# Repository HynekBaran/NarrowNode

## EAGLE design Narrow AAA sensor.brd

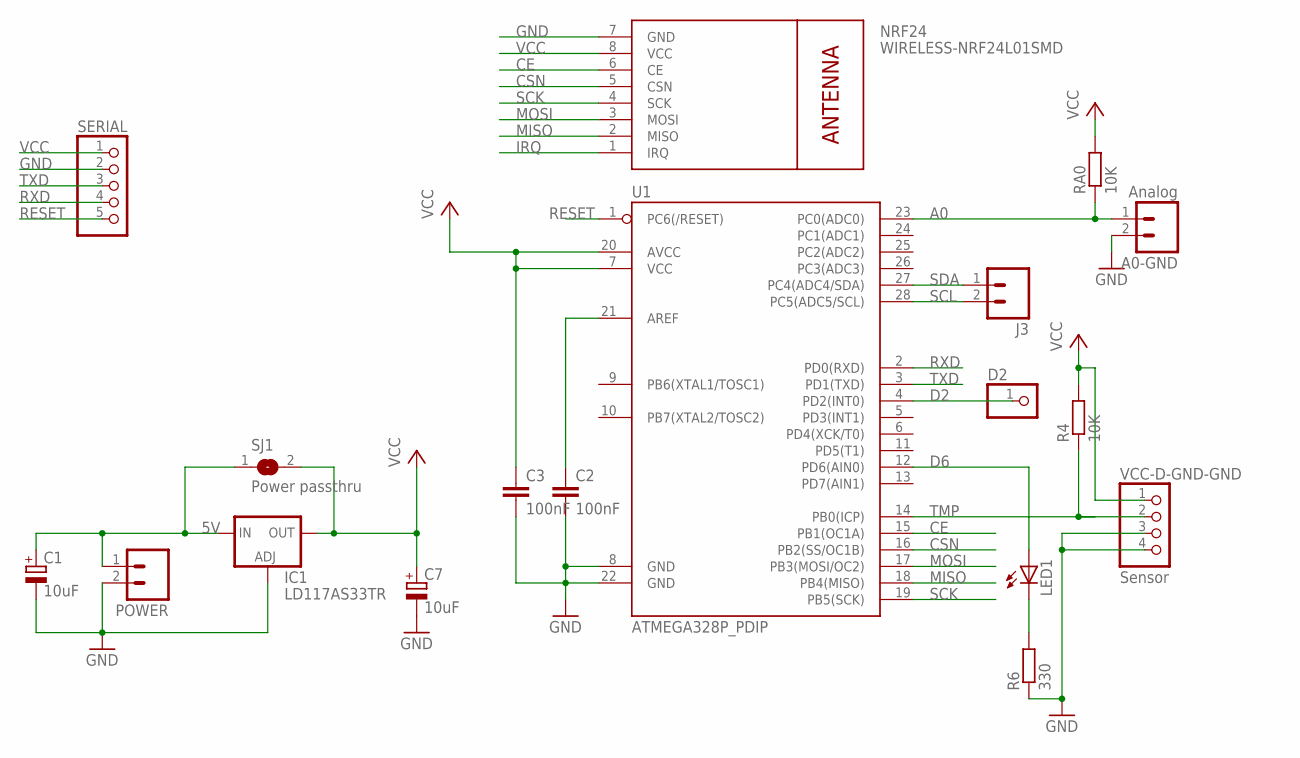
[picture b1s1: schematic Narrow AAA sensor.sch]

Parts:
A0-GND: Analog; 1X02
C1, C7: 10uF; E2,5-5
C2, C3: 100nF; C025-025X050
D2: PINHD-1X1; 1X01
IC1: LD117AS33TR; SOT223
J3: M021X02_NO_SILK; 1X02_NO_SILK
LED1: LED3MM
NRF24: WIRELESS-NRF24L01SMD; WIRELESS-NRF24L01-SMD
POWER: M021X02_NO_SILK; 1X02_NO_SILK
R4: 10K; 0204/7
R6: 330; 0204/7
RA0: 10K; 0204/7
SERIAL: PINHD-1X5; 1X05
SJ1: Power passthru; SJ
U1: ATMEGA328P_PDIP; DIL28-3
VCC-D-GND-GND: Sensor; 1X04

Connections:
5V: C1.+, IC1.3 (IN), POWER.1, SJ1.1
A0: A0-GND.1, RA0.1, U1.23 (PC0(ADC0))
CE: NRF24.6 (CE), U1.15 (PB1(OC1A))
CSN: NRF24.5 (CSN), U1.16 (PB2(SS/OC1B))
D2: D2.1, U1.4 (PD2(INT0))
D6: LED1.A, U1.12 (PD6(AIN0))
GND: A0-GND.2, C1.-, C2.2, C3.2, C7.-, IC1.1 (ADJ), NRF24.7 (GND), POWER.2, R6.1, SERIAL.2, U1.8 (GND), U1.22 (GND), VCC-D-GND-GND.3, VCC-D-GND-GND.4
IRQ: NRF24.1 (IRQ)
MISO: NRF24.2 (MISO), U1.18 (PB4(MISO))
MOSI: NRF24.3 (MOSI), U1.17 (PB3(MOSI/OC2))
unnamed: LED1.K (C), R6.2
unnamed: C2.1, U1.21 (AREF)
RESET: SERIAL.5, U1.1 (PC6(/RESET))
RXD: SERIAL.4, U1.2 (PD0(RXD))
SCK: NRF24.4 (SCK), U1.19 (PB5(SCK))
SCL: J3.2, U1.28 (PC5(ADC5/SCL))
SDA: J3.1, U1.27 (PC4(ADC4/SDA))
TMP: R4.1, U1.14 (PB0(ICP)), VCC-D-GND-GND.2
TXD: SERIAL.3, U1.3 (PD1(TXD))
VCC: C3.1, C7.+, IC1.4 (OUT), NRF24.8 (VCC), R4.2, RA0.2, SERIAL.1, SJ1.2, U1.7 (VCC), U1.20 (AVCC), VCC-D-GND-GND.1

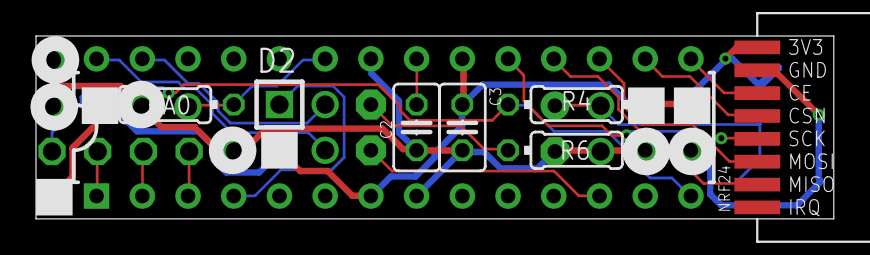
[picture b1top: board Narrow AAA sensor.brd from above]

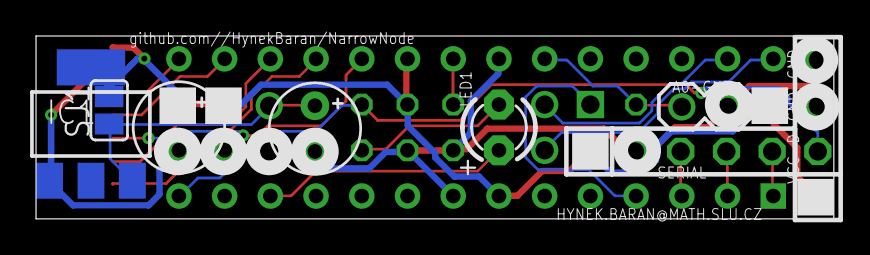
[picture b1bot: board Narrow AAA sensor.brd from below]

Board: 2 copper layers, 44.3 x 10.2 mm, 18 parts (8 on the bottom side), 19 nets.

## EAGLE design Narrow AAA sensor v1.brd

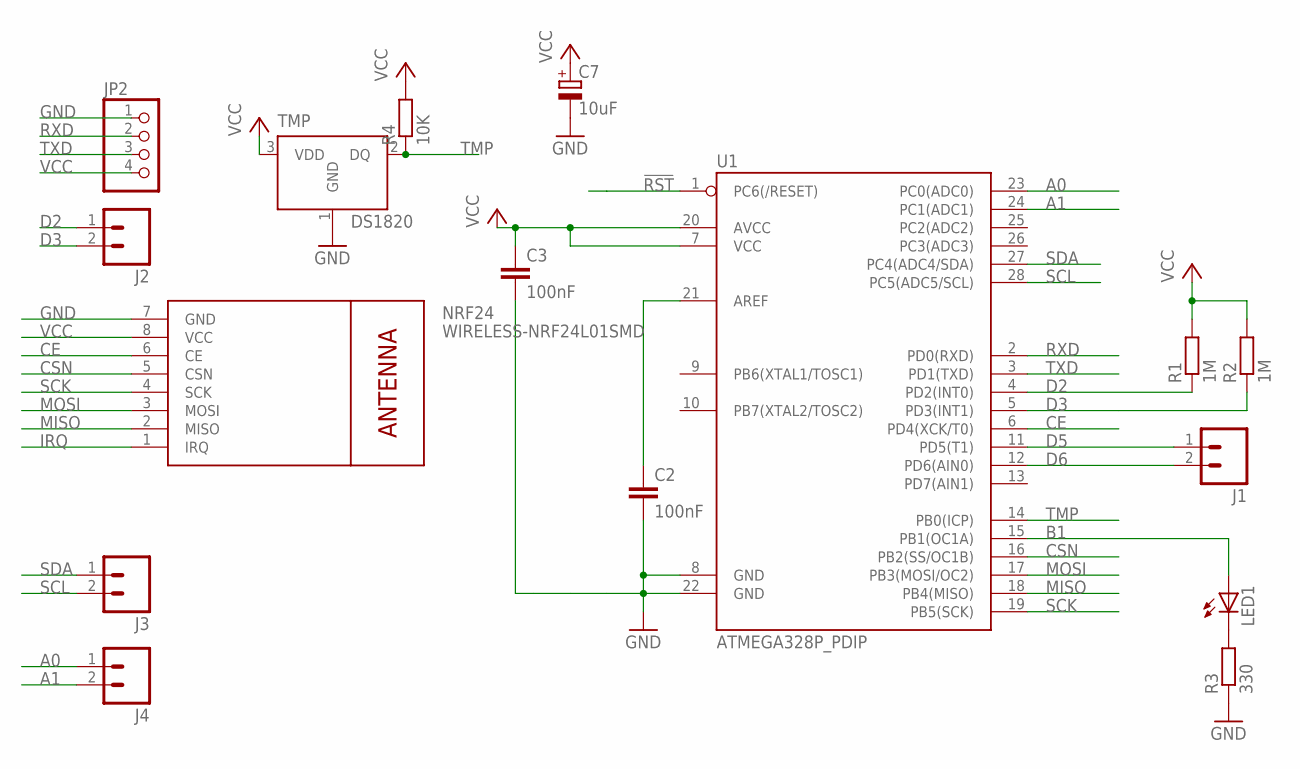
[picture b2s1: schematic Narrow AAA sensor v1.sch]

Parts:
C2, C3: 100nF; C025-025X050
C7: 10uF; E2,5-5
J1, J2: M02PTH; 1X02
J3, J4: M021X02_NO_SILK; 1X02_NO_SILK
JP2: PINHD-1X4; 1X04
LED1: LED3MM
NRF24: WIRELESS-NRF24L01SMD; WIRELESS-NRF24L01-SMD
R1, R2: 1M; 0204/7
R3: 330; 0204/7
R4: 10K; 0204/7
TMP: DS1820; TO-92
U1: ATMEGA328P_PDIP; DIL28-3

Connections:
!RST: U1.1 (PC6(/RESET))
A0: J4.1, U1.23 (PC0(ADC0))
A1: J4.2, U1.24 (PC1(ADC1))
B1: LED1.A, U1.15 (PB1(OC1A))
CE: NRF24.6 (CE), U1.6 (PD4(XCK/T0))
CSN: NRF24.5 (CSN), U1.16 (PB2(SS/OC1B))
D2: J2.1, R1.1, U1.4 (PD2(INT0))
D3: J2.2, R2.1, U1.5 (PD3(INT1))
D5: J1.1, U1.11 (PD5(T1))
D6: J1.2, U1.12 (PD6(AIN0))
GND: C2.2, C3.2, C7.-, JP2.1, NRF24.7 (GND), R3.1, TMP.1 (GND), U1.8 (GND), U1.22 (GND)
IRQ: NRF24.1 (IRQ)
MISO: NRF24.2 (MISO), U1.18 (PB4(MISO))
MOSI: NRF24.3 (MOSI), U1.17 (PB3(MOSI/OC2))
unnamed: LED1.K (C), R3.2
unnamed: C2.1, U1.21 (AREF)
RXD: JP2.2, U1.2 (PD0(RXD))
SCK: NRF24.4 (SCK), U1.19 (PB5(SCK))
SCL: J3.2, U1.28 (PC5(ADC5/SCL))
SDA: J3.1, U1.27 (PC4(ADC4/SDA))
TMP: R4.1, TMP.2 (DQ), U1.14 (PB0(ICP))
TXD: JP2.3, U1.3 (PD1(TXD))
VCC: C3.1, C7.+, JP2.4, NRF24.8 (VCC), R1.2, R2.2, R4.2, TMP.3 (VDD), U1.7 (VCC), U1.20 (AVCC)

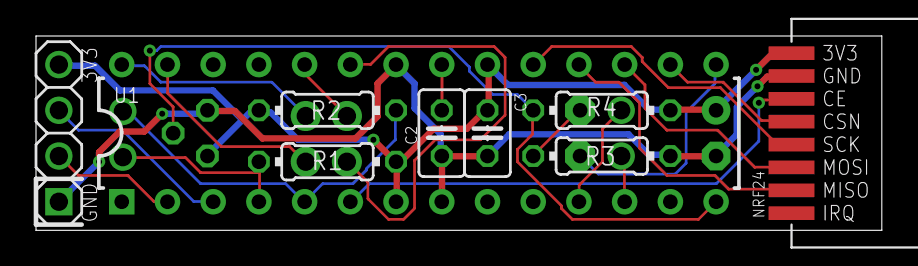
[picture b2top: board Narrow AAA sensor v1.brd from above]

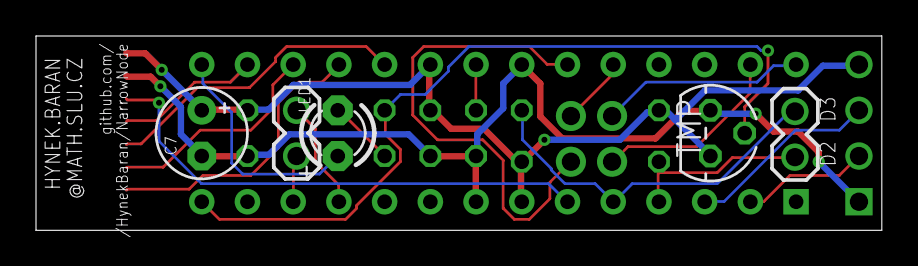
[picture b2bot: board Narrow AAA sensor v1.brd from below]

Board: 2 copper layers, 47.0 x 10.8 mm, 16 parts (5 on the bottom side), 21 nets.

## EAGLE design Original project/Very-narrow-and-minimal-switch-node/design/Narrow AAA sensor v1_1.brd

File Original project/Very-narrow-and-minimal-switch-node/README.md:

**What izz dizz ???**

**_
### Version 1-0:
_**

This board is a 1 trick pony (it's not very smart). It is meant to allow connection of 2 switches on pins D2 and D3 of the processor. It uses the SMD version of the NRF24L01+ module, runs the atmega328p on internal oscillator and is meant to sleep most of the time.

There is space for a pull up resistor (any value between 1M Ohm and 10M Ohm is fine) for each of the two pins (D2 and/or D3).
```
R1 is for D2
R2 is for D3

```
A led is connected to pin D8 via a 330 Ohm resistor (R3). An electrolytical capacitor of 10uF is provided to decouple the Vcc and Gnd pins of the NRF24L01+ smd module. Two 100nF ceramic capacitors are decoupling the power line (Vcc/AVcc and ARef).

And that is it. No temp sensor, no voltage divider, no prototyping area, no FTDI connector, no ISP connector, no crystal.

Just a very narrow node based on @m26872's original idea.

**How can you use it ?**

Since there are two pins for digital signals and 2 pins for power, you still have a few options.

Lets look at the easy part first: power

This boards needs DC power between 1.9V DC (the minimum the NRF24L01+ module needs to function) and maximum 3.6V DC (again a limitation of the NRF24L01+). The processor can handle a wider range (1.8v - 5.1V), but as said, the radio sets the limits on the allowed voltages. There are two pins at the edge called "GND" and "3V3", function should be obvious. GND has a square pad and sits at the edge of the board.

For further orientation, hold the board so that the radio is on the right hand side, the "GND" terminal sits in the top left corner.

Now for the two pins called "D2" and "D3".

These two pins are connected directly to the pins of the processor called ... wait for it ... "D2" and "D3". I'm feeling very pleased with knowing this now :-), moving on.

If you do not mount the pull up resistors, you can use these pins as outputs. Seriously? Yes !!!! Outputs ! We can give "1" or "0" on both D2 and D3 so this could be used for control of something. Personally not my use case, but it is possible.

**1 switch input**

If you need only 1 pin to connect a switch (magnetic, mechanical, reed, optical,...), but you are missing a "GND" pin, then there is a solution.

You do NOT mount the pull up resistor for D3, and define pin D3 as an output LOW pin. This sets D3 equal to ground. You will need to define this in the setup procedure of the sketch.

Then you will need to have mounted the pull up resistor for D2 (on the board it is marked with "R1"), and the header pin called "D2" becomes the input.

You would get the following on the header:

```
square pad: GND    -----+ power terminal, houurrah !
round pad: VCC    ------+
round pad: D2 (input)     -------+
round pad: D3 (= GND)     -------+ switch terminal, yeah !
```

**powering something with low consumption**

You can set both pins D2 and D3 of the processor to OUTPUT, do not mount the pull up resistors, do not activate the internal PullUPs, and by setting one of the pins to HIGH and the other to LOW you can power something. You will need to take care that a maximum of 20mA is consumed, as this is the recommended maximum amperage the pins of the atmega328 can drive or source.

**Now for another option: two switches.**

This is easy to understand: when both pull up resistors are mounted and both the processor pins D2 and D3 are set to INPUT, then the header pins are ready to receive GND or 3V3. You will need to use the power "GND" pin as ground reference.

The nice thing about D2 and D3 as input pins, is that they can be set as hardware interrupt pins to wake up the processor from power down (MySensor "SLEEP(0,CHANGE,1,CHANGE,0)" function).

Power consumption is measured at 7.7 uA maximum during sleep (2 open switches) and 7.0 uA minimum (2 closed switches), if using the Watchdog timer to wake up every now and then to send battery level. Under full power down (as the function call above does) the power consumption will be lower but I did not measure it yet.

This is my preferred use case, hence the name of this node.

**about Passive Infra Red sensing**

If a PIR sensor is powered by 3V3, and it can produce a HIGH signal, you could connect a switch (on a door or window) to pin D2. And you still can connect the PIR to D3. Any change on D2 or D3 would wake up the processor.

Regarding PIR sensors to use: only use 3V3 versions, not the ones which need 5V, because they would drive the input pin too high. Not a disaster if you do this, but I'm not sure how long the atmega328 would accept it before failing.

**Other sensors ???**

Indeed, any other sensor which produces a logical HIGH or LOW can be used as input on D2 or D3. Just make sure that the sensor is powered by itself, or works within the limits of the battery voltage powering the node.

**Measuring and reporting battery voltage**

Battery voltage is measured by using the internal reference and the Vcc library (so no voltage divider needed). My DEV library based sketch is included and uses this library. As we are not allowed to power the board above 3.6V DC, we can use the "hidden" voltage measuring technique. Look at the provided sketch for this (look for "vcc.something").
This internal measuring technique has an error of around 10%, so do not expect accurate readings. Use it to decide when to replace the battery. I set an alarm in my controller, when a node reports a battery level below 2V. This gives me time to go buy batteries and replace them (usually more than a week time between first alarm and replacement, I'm slow ...).

**About the included sketch**

-- important: the sketch was written using the Development library, so not version 1.5.x but the newest of the newest of the best ;-). It may look like some things are missing in the code, that would be true if you have MySensors library 1.5.x

In my sketch, the battery voltage is sent every time the processor wakes up. If nothing changes at the input pins, then the node will wake up every 23 hours to report battery voltage (not battery percent, only battery voltage).
If a signal change is seen at the pins, the battery voltage is measured and sent first. This allows the signal at the input pins to settle to a stable state (this is software debounce), and if the stable state at the pin is different from previous reporting, it is sent to the gateway/controller.

**about the hardware**

You can get this board at OSH Park:

v1-0  https://oshpark.com/shared_projects/LAJtrt2k

v1-1  https://oshpark.com/shared_projects/GTBdUqTV

I'm using a Optiboot 6.2 version which expects a baudrate of 38400. Any boot loader is fine, as long as you set the fuses to 8MHz internal oscillator. You will need to flash the atmega328p before you plug it into this board, so make sure it works in another setup or on the breadboard before you push it hard into the socket.

There is no way to reprogram the board, not via FTDI, not over the air, not by jedi hand waving. Only when you pull out the processor and program it in another setup, can you change anything. Remember: this is a minimal board, it does 1 thing (or 2 if you use two pins), and it can notify your controller of whatever it does or sees. But it is certainly not a versatile node like it's godfather (the slim 2AA battery node by m26872). This is a minion.

**_
### Version 1-1:
_**

In a comment someone suggested to add I2C capability, and actually this is relatively easy. So I added solder jumpers to give the option.

There are two solder jumpers called SJ1 and SJ2. Together they define which signals are presented on PIN1 and PIN2 of the header at the edge of the board.

The silkscreen also shows this. The consequence of this change is that you can not add 2 pull up resistors, but just 1 (for D2). Here are the options.

```
SJ1:
+--SDA-A4
+--PIN1--+
   D2----+
```
With SJ1 you choose to connect either D2 to PIN1 of you choose A4 connected to PIN1. This is independent of the other jumper.
If you want to use I2C, you will need to connect SCL-A5 as well on SJ2.

```
SJ2:
+--SCL-A5
+--PIN2---+
   GND----+
```
With this solder jumper you can connect GND to PIN2, or you choose A5 connected to PIN2. If I2C needs to be used, then A4 needs to be connected, and the I2C functions need to be called.

Here are all possible combinations you can make on the header

```
GND
D2
GND
VCC
```

```
GND
D2
A5
VCC
```

```
GND
A4
GND
VCC
```

```
GND
A4
A5
VCC
```

In this last case you can use the pins as analog inputs, or as the I2C "ports" SDA/SCL:

```
GND
SDA
SCL
VCC
```

This is - by pure coincidence - also the pinout of the small SMD versions of a SI7021 board.

Second remark on I2C: this node does not provide pull up resistors for I2C, so if needed, the connecting device needs to provide the I2C pull up resistors. Most I2C sensor boards do this, but check anyway.

**Using D6**

Version 1-1 of the board is slightly different than v1-0 in another aspect: instead of using pin D8 to allow flashing a LED, I now use pin D6. I have added a bootloader (based on Optiboot 6.2) which will flash the LED on pin D6 three times when reset is given. You can find the hex file in the design files.

Why pin D6 ? Because it can be driven with Pulse Width Modulation via the function AnalogWrite(). Pin D8 is a pure on/off pin.

If you skip mounting R3 and put a wire instead, then you have D6 and GND at the pads where normally one would solder the LED. This means that if you can live without the LED, you actually have access to a third processor pin. In this case D6.

I thought D6 would be more versatile then D8. And for those that do use a LED, D6 allows dimming effects (whereas D8 was only on or off).

**RESET pullup**

Finally, another change between v1-0 and v1-1 is how I handle the reset pin. I left it floating in v1-0. So far that has not caused any problems, except in 1 board. So I decided to pull up RESET just to be sure. As I had to choose between giving GND or a second interrupt cable pin on the external connector, I decided in favour of GND. This node is simple and cheap enough to handle a single switch. Handling 2 switches is possible, but not really needed. And we can still use an analog pin as digital input. And if you skip mounting the LED to get a third pin (input or PWM capable output): D6.

The fact that only 1 pin can wake the node from deep sleep is a tradeoff I accept.

**Version history**

JAN 2016: Added Version 1 info.
This is revision 1 of this board. It is meant as a test board for mounting the SMD version of the NRF24L01+ (a quick hack I admit). A possible improvement is to add two more holes next to R1 and R2, so they could be used as pull down resistors.
The silkscreen (the text on the board) can be better, and marking the names of the header pins on he bottom side is something I should have done (using the boards tells me this now). The numbering of the capacitors does not start at C1, because originally I had more of them on the board. I did not renumber after cleaning out all unnecessary stuff. I may do that at a later stage if I revisit this design.
The designed is licensed under CERN OHL V1.2 and is fully Open Hardware.

13-FEB-2016: added v1-1 files (tested) and use cases.
Explanation of the solder jumpers and what you could do with the pins in various combinations.
15-FEB-2016: added bootloader
Added a recompiled Optiboot 6.2 with LED flash on pin D6, for 8MHz internal oscillator (or 8MHz crystal if you use this in another board) and baudrate of 38400 for uploads.

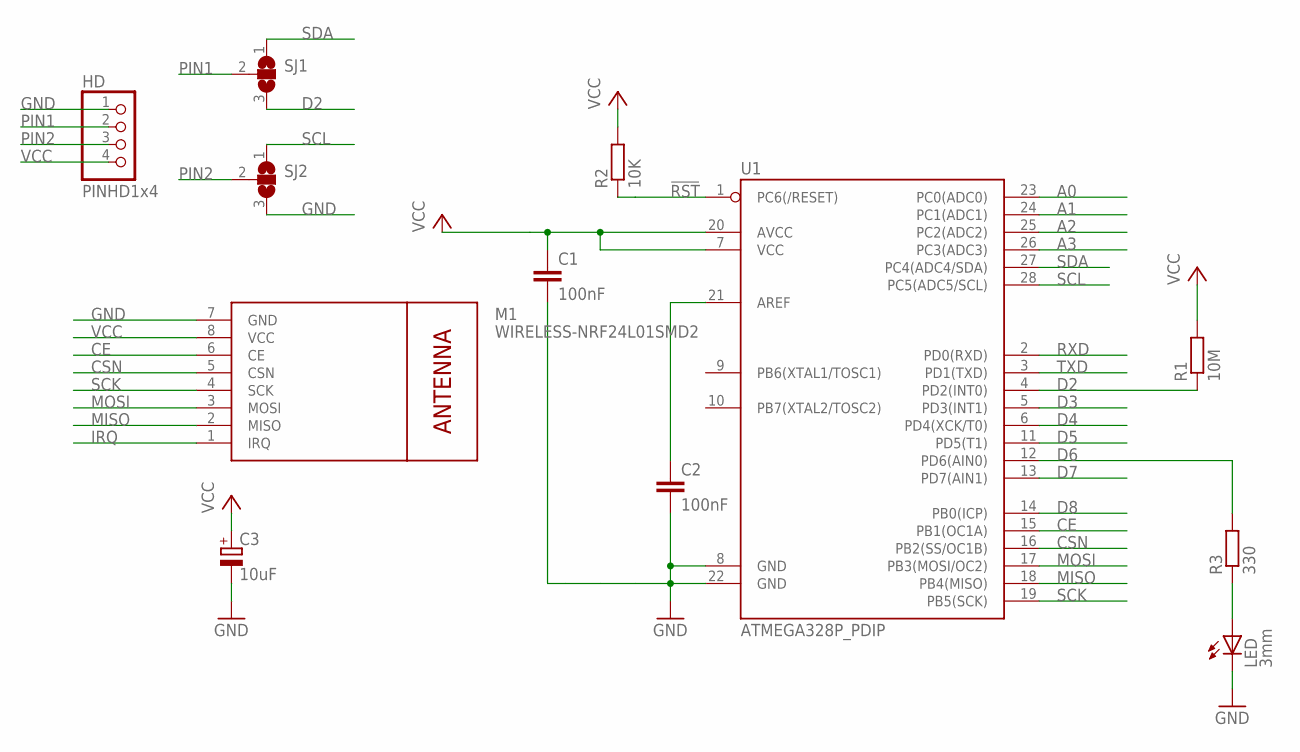
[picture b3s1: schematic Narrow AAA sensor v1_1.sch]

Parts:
C1, C2: 100nF; C025-025X050
C3: 10uF; E2,5-5
HD: PINHD1x4; 1X04
LED: 3mm; LED3MM
M1: WIRELESS-NRF24L01SMD2; WIRELESS-NRF24L01-SMD-2
R1: 10M; 0204/7
R2: 10K; 0204/7
R3: 330; 0204/7
SJ1, SJ2: SJ2W; SJ_2
U1: ATMEGA328P_PDIP; DIL28-3

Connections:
!RST: R2.1, U1.1 (PC6(/RESET))
A0: U1.23 (PC0(ADC0))
A1: U1.24 (PC1(ADC1))
A2: U1.25 (PC2(ADC2))
A3: U1.26 (PC3(ADC3))
CE: M1.6 (CE), U1.15 (PB1(OC1A))
CSN: M1.5 (CSN), U1.16 (PB2(SS/OC1B))
D2: R1.1, SJ1.3, U1.4 (PD2(INT0))
D3: U1.5 (PD3(INT1))
D4: U1.6 (PD4(XCK/T0))
D5: U1.11 (PD5(T1))
D6: R3.2, U1.12 (PD6(AIN0))
D7: U1.13 (PD7(AIN1))
D8: U1.14 (PB0(ICP))
GND: C1.2, C2.2, C3.-, HD.1, LED.K (C), M1.7 (GND), SJ2.3, U1.8 (GND), U1.22 (GND)
IRQ: M1.1 (IRQ)
MISO: M1.2 (MISO), U1.18 (PB4(MISO))
MOSI: M1.3 (MOSI), U1.17 (PB3(MOSI/OC2))
unnamed: LED.A, R3.1
unnamed: C2.1, U1.21 (AREF)
PIN1: HD.2, SJ1.2
PIN2: HD.3, SJ2.2
RXD: U1.2 (PD0(RXD))
SCK: M1.4 (SCK), U1.19 (PB5(SCK))
SCL: SJ2.1, U1.28 (PC5(ADC5/SCL))
SDA: SJ1.1, U1.27 (PC4(ADC4/SDA))
TXD: U1.3 (PD1(TXD))
VCC: C1.1, C3.+, HD.4, M1.8 (VCC), R1.2, R2.2, U1.7 (VCC), U1.20 (AVCC)

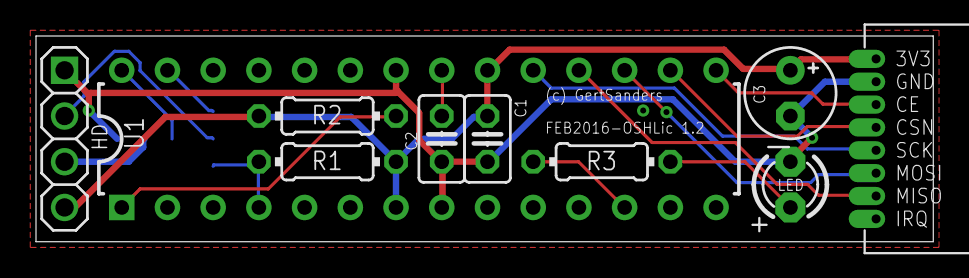
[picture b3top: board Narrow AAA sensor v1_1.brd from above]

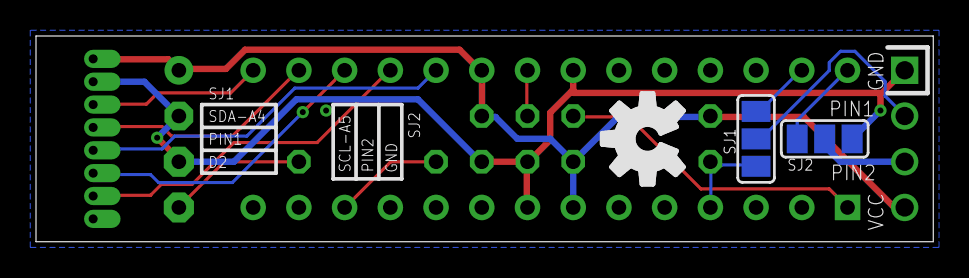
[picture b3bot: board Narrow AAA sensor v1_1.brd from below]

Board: 2 copper layers, 49.8 x 11.4 mm, 13 parts (3 on the bottom side), 16 nets.

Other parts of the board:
U$1: OSHWLOGO_TOL_0.2

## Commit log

2016-11-09 Initial state
2016-11-09 Text added
2016-12-15 FIXed missing TMP wire
2017-03-15 V2 RC1 * smaller size * respecting mysensors radio connection (CE=PB1) * Vcc regulator * no pull-ups except TMP * single LED on D6
2017-09-20 https://PCBs.io/share/zM3DO

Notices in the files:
Original project/Very-narrow-and-minimal-switch-node/README.md:
The designed is licensed under CERN OHL V1.2 and is fully Open Hardware.
parts and their libraries:
SparkFun-Connectors: Licensing: Creative Commons ShareAlike 4.0 International - https://creativecommons.org/licenses/by-sa/4.0
